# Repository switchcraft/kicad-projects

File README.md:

# kicad-projects
KiCad Project files, schematic files, layout files and netlists

All contributions should adhere to the Kicad library convention, just like the standard KiCad library. 
See: https://github.com/KiCad/kicad-library/wiki/Kicad-Library-Convention

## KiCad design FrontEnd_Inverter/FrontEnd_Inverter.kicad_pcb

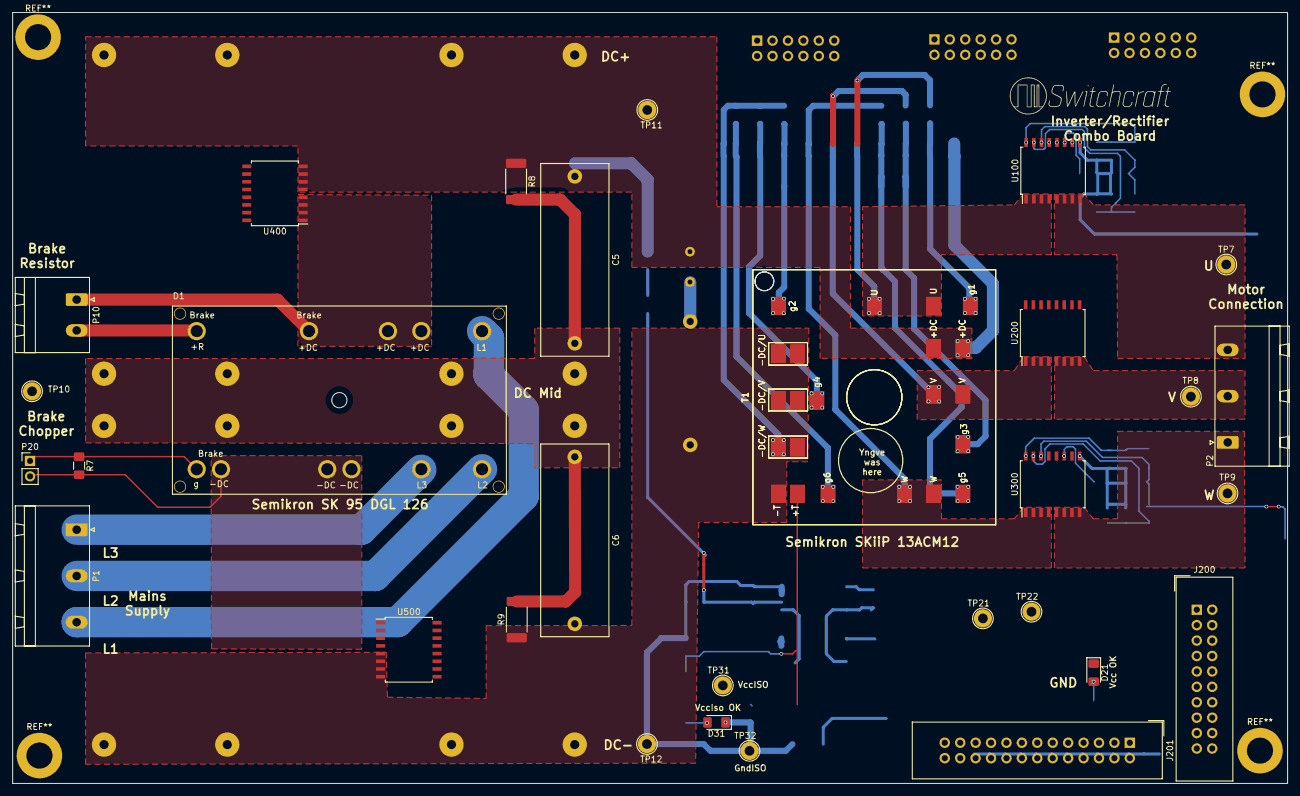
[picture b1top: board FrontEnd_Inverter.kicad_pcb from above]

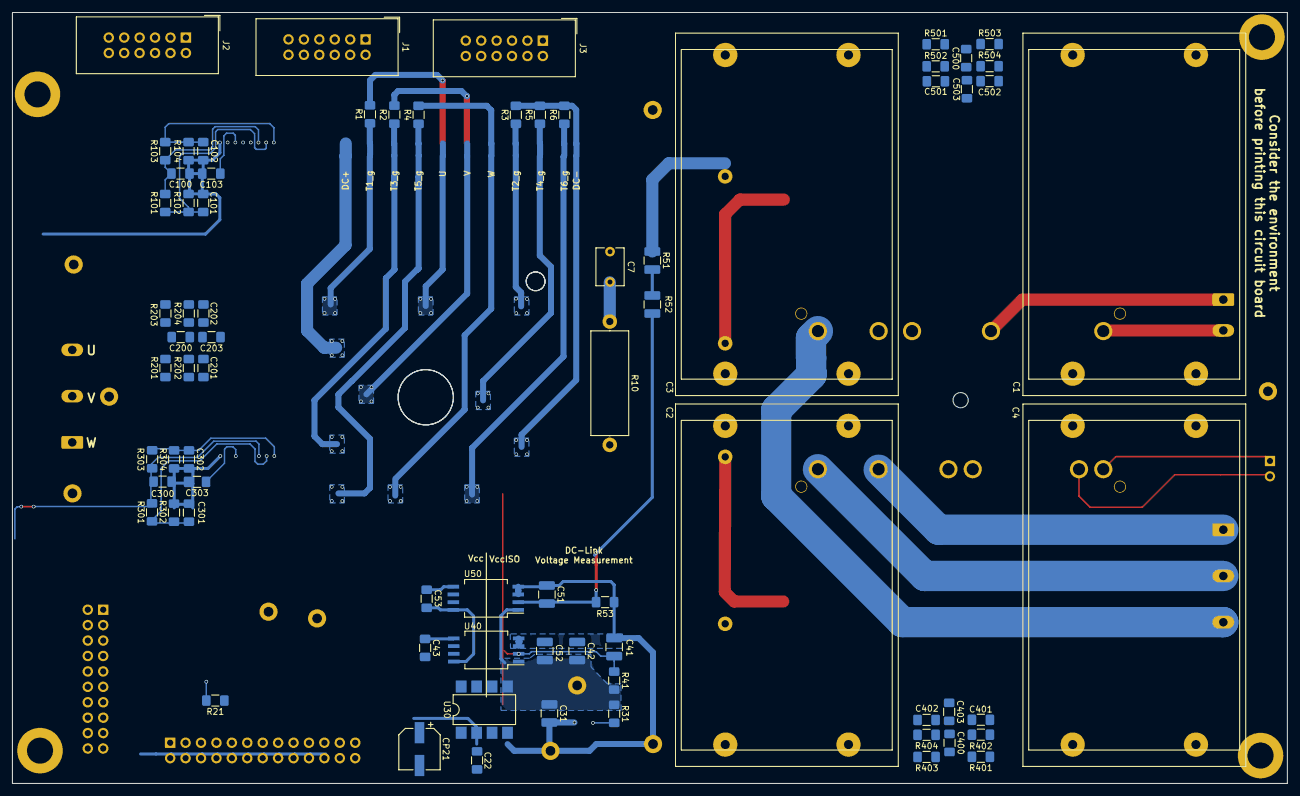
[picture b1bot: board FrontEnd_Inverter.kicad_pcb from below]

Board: 4 copper layers, 210.0 x 127.0 mm, 104 parts (73 on the bottom side), 66 nets.

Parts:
C1, C2, C3, C4: 50uF; Panasonic_EZPE80506MTA
C5, C6: 5uF; C_Rect_L31.5mm_W11.0mm_P27.50mm_MKS4
C7: 22pF; C_Disc_D6.0mm_W4.4mm_P5.00mm
C22: 10nF; C_1206_3216Metric_Pad1.42x1.75mm_HandSolder
C31: 10uF; C_1210_3225Metric_Pad1.42x2.65mm_HandSolder
C41, C51: 100pF; C_1210_3225Metric_Pad1.42x2.65mm_HandSolder
C42, C52: 100nF; C_1210_3225Metric_Pad1.42x2.65mm_HandSolder
C43, C53, C100, C200, C300, C400, C500: 100nF; C_1206_3216Metric_Pad1.42x1.75mm_HandSolder
C101, C102, C103, C201, C202, C203, C301, C302, C303, C401, C402, C403, C501, C502, C503: 1nF; C_1206_3216Metric_Pad1.42x1.75mm_HandSolder
CP21: 10uF; CP_Elec_6.3x7.7
D1: SK_95_DGL_126
D21, D31: GREEN; LED_1206_3216Metric_Pad1.42x1.75mm_HandSolder
J1, J2, J3: GateDriverConn; IDC-Header_2x06_P2.54mm_Vertical
J200: AuxConnector_Analog; IDC-Header_2x10_P2.54mm_Vertical
J201: DigOut_Connector; IDC-Header_2x13_P2.54mm_Vertical
P1, P2: CONN_01X03; PhoenixContact_GMSTBA_2,5_3-G-7,62_1x03_P7.62mm_Horizontal
P10: CONN_01X02; PhoenixContact_MSTBA_2,5_2-G-5,08_1x02_P5.08mm_Horizontal
P20: CONN_01X02; PinHeader_1x02_P2.54mm_Vertical
R1, R2, R3, R4, R5, R6, R7, R41: 100k; R_1206_3216Metric_Pad1.42x1.75mm_HandSolder
R8, R9: 200k; R_2512_6332Metric_Pad1.52x3.35mm_HandSolder
R10: 5; R_Axial_DIN0617_L17.0mm_D6.0mm_P20.32mm_Horizontal
R21, R31: 1250; R_1206_3216Metric_Pad1.42x1.75mm_HandSolder
R51, R52: 2.7M; R_1210_3225Metric_Pad1.42x2.65mm_HandSolder
R53: 20k; R_1206_3216Metric_Pad1.42x1.75mm_HandSolder
R101, R103, R201, R203, R301, R303, R401, R403, R501, R503: 2M; R_1206_3216Metric_Pad1.42x1.75mm_HandSolder
R102, R104, R202, R204, R302, R304, R402, R404, R502, R504: 326k; R_1206_3216Metric_Pad1.42x1.75mm_HandSolder
T1, T1#2: SKiiP_13ACM12V18
TP7: U; TestPoint_Loop_D2.60mm_Drill1.6mm_Beaded
TP8: V; TestPoint_Loop_D2.60mm_Drill1.6mm_Beaded
TP9: W; TestPoint_Loop_D2.60mm_Drill1.6mm_Beaded
TP10: DC_MID; TestPoint_Loop_D2.60mm_Drill1.6mm_Beaded
TP11: DC+; TestPoint_Loop_D2.60mm_Drill1.6mm_Beaded
TP12: DC-; TestPoint_Loop_D2.60mm_Drill1.6mm_Beaded
TP21: VCC; TestPoint_Loop_D2.60mm_Drill1.6mm_Beaded
TP22: GND; TestPoint_Loop_D2.60mm_Drill1.6mm_Beaded
TP31: VCC_ISO; TestPoint_Loop_D2.60mm_Drill1.6mm_Beaded
TP32: GND_ISO; TestPoint_Loop_D2.60mm_Drill1.6mm_Beaded
U30: ISE0505A-H; SMDIP-8_W7.62mm
U40, U50: ACPL-C87B; SSO-8_6.8x5.9mm_P1.27mm_Clearance8mm
U100, U200, U300, U400, U500: ACS720KLATR-35B; SOIC-16W_7.5x10.3mm_P1.27mm

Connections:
+VDC: C1.1, C3.1, C5.1, C7.1, J1.1, J1.2, J2.1, J2.2, J3.1, J3.2, R8.1, R51.1, T1.7, T1.8, T1#2.7, T1#2.8, TP11.1, U400.5, U400.6, U400.7, U400.8
BC_gate: D1.28, P20.1, R7.1
DC+_in: D1.4, D1.5, D1.9, P10.1, U400.1, U400.2, U400.3, U400.4
DC-_in: D1.21, D1.22, D1.27, P20.2, R7.2, U500.1, U500.2, U500.3, U500.4
DC-_out: J1.10, J1.12, J2.10, J2.12, J3.10, J3.12, R2.1, R4.2, R6.2
DC_Meas+: J200.11, U50.7
DC_Meas-: J200.13, U50.6
FAULT_F_DC+: J201.13, U400.13
FAULT_F_DC-: J201.17, U500.13
FAULT_F_U: J201.1, U100.13
FAULT_F_V: J201.5, U200.13
FAULT_F_W: J201.9, U300.13
FAULT_S_DC+: J201.15, U400.10
FAULT_S_DC-: J201.19, U500.10
FAULT_S_U: J201.3, U100.10
FAULT_S_V: J201.7, U200.10
FAULT_S_W: J201.11, U300.10
GND: C22.2, C43.1, C53.2, C100.2, C101.2, C102.2, C103.2, C200.2, C201.2, C202.2, C203.2, C300.2, C301.2, C302.2, C303.2, C400.2, C401.2, C402.2, C403.2, C500.2, C501.2, C502.2, C503.2, CP21.2, D21.1, J200.2, J200.4, J200.6, J200.8, J200.10, J200.12, J200.14, J200.16, J200.18, J200.20, J201.2, J201.4, J201.6, J201.8, J201.10, J201.12, J201.14, J201.16, J201.18, J201.20, J201.22, J201.24, J201.26, R102.1, R104.1, R202.1, R204.1, R302.1, R304.1, R402.1, R404.1, R502.1, R504.1, TP22.1, U30.1, U40.5, U50.5, U100.9, U200.9, U300.9, U400.9, U500.9
unnamed: C1.2, C2.1, C3.2, C4.1, C5.2, C6.1, R8.2, R9.1, TP10.1
unnamed: C7.2, R10.1
unnamed: C51.1, R52.2, R53.1, U50.2
unnamed: C101.1, R101.1, R102.2, U100.15
unnamed: C102.1, R103.1, R104.2, U100.16
unnamed: C103.1, U100.11
unnamed: C201.1, R201.1, R202.2, U200.15
unnamed: C202.1, R203.1, R204.2, U200.16
unnamed: C203.1, U200.11
unnamed: C301.1, R301.1, R302.2, U300.15
unnamed: C302.1, R303.1, R304.2, U300.16
unnamed: C303.1, U300.11
unnamed: C401.1, R401.1, R402.2, U400.15
unnamed: C402.1, R403.1, R404.2, U400.16
unnamed: C403.1, U400.11
unnamed: C501.1, R501.1, R502.2, U500.15
unnamed: C502.1, R503.1, R504.2, U500.16
unnamed: C503.1, U500.11
unnamed: D1.1, P1.3
unnamed: D1.14, P10.2
unnamed: D1.15, P1.2
unnamed: D1.18, P1.1
unnamed: D21.2, R21.2
unnamed: D31.2, R31.2
unnamed: R51.2, R52.1
T1_g: J1.3, J1.4, R1.1, T1.1, T1#2.1
T2_g: J1.9, J1.11, R2.2, T1.2, T1#2.2
T3_g: J2.3, J2.4, R3.1, T1.3, T1#2.3
T4_g: J2.9, J2.11, R4.1, T1.4, T1#2.4
T5_g: J3.3, J3.4, R5.1, T1.5, T1#2.5
T6_g: J3.9, J3.11, R6.1, T1.6, T1#2.6
T+: C41.1, R41.1, T1.21, T1#2.21, U40.2
T+_out: J200.15, U40.7
T-: C2.2, C4.2, C6.2, C31.2, C41.2, C42.1, C51.2, C52.2, D31.1, R9.2, R10.2, R53.2, T1.9, T1.10, T1.11, T1.12, T1.13, T1.14, T1.22, T1#2.9, T1#2.10, T1#2.11, T1#2.12, T1#2.13, T1#2.14, T1#2.22, TP12.1, TP32.1, U30.4, U40.3, U40.4, U50.3, U50.4, U500.5, U500.6, U500.7, U500.8
T-_out: J200.17, U40.6
U: J1.5, J1.6, J1.7, J1.8, R1.2, T1.15, T1.16, T1#2.15, T1#2.16, U100.1, U100.2, U100.3, U100.4
U_out: P2.3, TP7.1, U100.5, U100.6, U100.7, U100.8
V: J2.5, J2.6, J2.7, J2.8, R3.2, T1.17, T1.18, T1#2.17, T1#2.18, U200.1, U200.2, U200.3, U200.4
VCC: C22.1, C43.2, C53.1, C100.1, C200.1, C300.1, C400.1, C500.1, CP21.1, J201.23, R21.1, R101.2, R103.2, R201.2, R203.2, R301.2, R303.2, R401.2, R403.2, R501.2, R503.2, TP21.1, U30.2, U40.8, U50.8, U100.14, U200.14, U300.14, U400.14, U500.14
VCC_ISO: C31.1, C42.2, C52.1, R31.1, R41.2, TP31.1, U30.5, U40.1, U50.1
VI_DC+: J200.7, U400.12
VI_DC-: J200.9, U500.12
VI_U: J200.1, U100.12
VI_V: J200.3, U200.12
VI_W: J200.5, U300.12
V_out: P2.2, TP8.1, U200.5, U200.6, U200.7, U200.8
W: J3.5, J3.6, J3.7, J3.8, R5.2, T1.19, T1.20, T1#2.19, T1#2.20, U300.1, U300.2, U300.3, U300.4
W_out: P2.1, TP9.1, U300.5, U300.6, U300.7, U300.8

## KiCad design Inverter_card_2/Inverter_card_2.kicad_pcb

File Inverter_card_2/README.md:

# Inverter Card 2

Inverter circuit board for Semikron IGBT/SiC module. 

Features connections to gatedrivers and motor output. Voltage and temperature measurement through isolation amplifiers. Three phase output current measurement through hall-effect sensors.

This card is designed to sit on top of the DC-link capacitors. The board is designed for a no-load DC-link voltage of 565V.

## References
DC-link capacitor sizing: <https://www.ecicaps.com/wp-content/uploads/IEMDC_2009_11310_Final_Rev_4.pdf>

## Datasheets

### Capacitors
<http://datasheet.octopart.com/EZP-E80506MTA-Panasonic-datasheet-21212084.pdf>

### Power supply
<http://datasheet.octopart.com/ISE0505A-XP-Power-datasheet-41209557.pdf>

### Sensors
<http://datasheet.octopart.com/ACS758ECB-200U-PFF-T-Allegro-MicroSystems-LLC-datasheet-8491666.pdf>
<http://datasheet.octopart.com/ACPL-C87B-000E-Broadcom-datasheet-68302108.pdf>

### Transistors
<https://www.semikron.com/dl/service-support/downloads/download/semikron-datasheet-skiip-13acm12v18-25238280/>

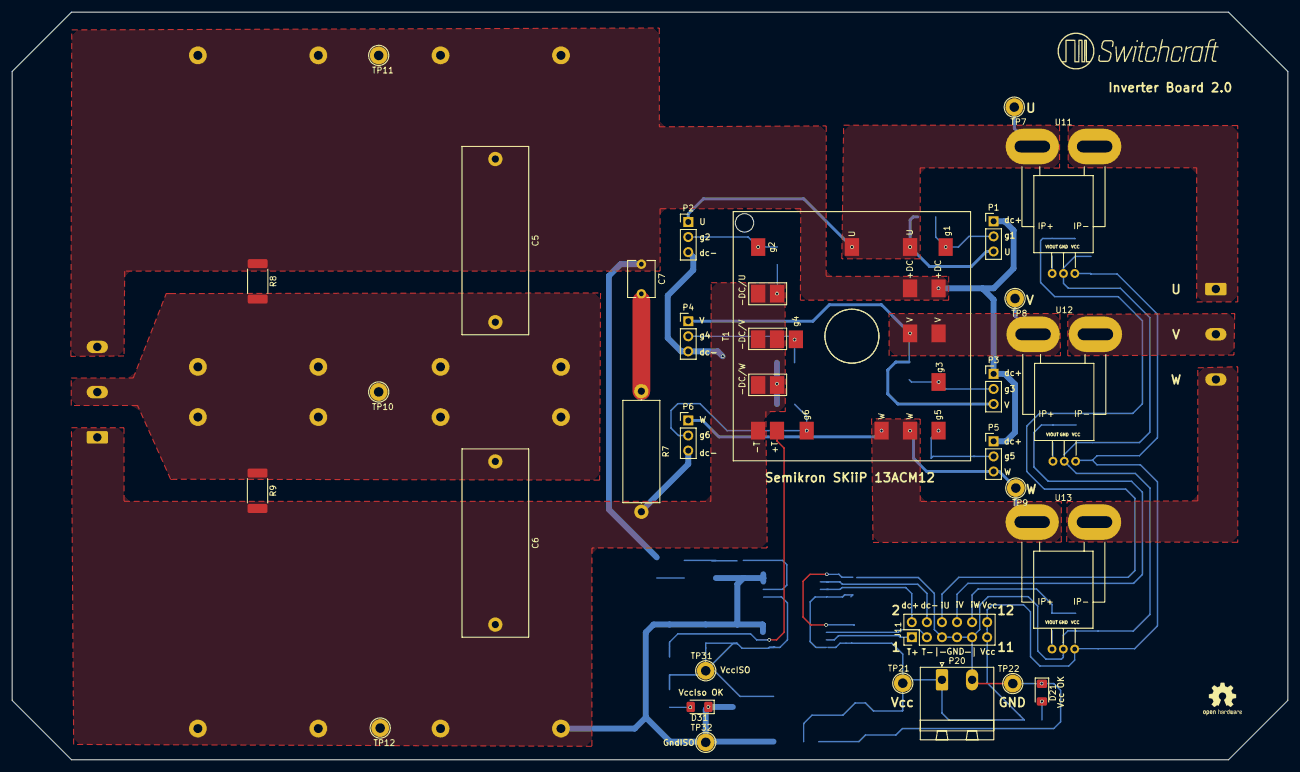
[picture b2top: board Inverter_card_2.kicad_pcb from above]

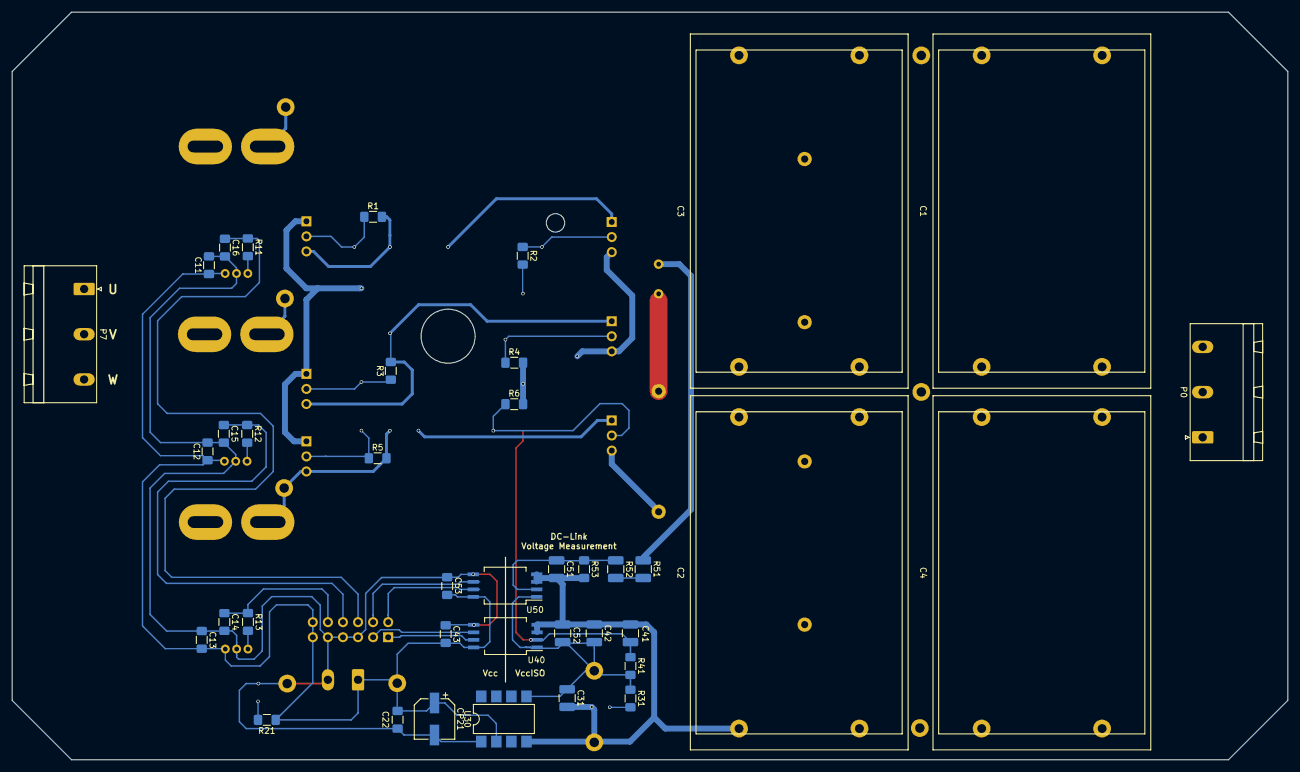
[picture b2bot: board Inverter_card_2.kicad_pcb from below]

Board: 4 copper layers, 215.0 x 126.0 mm, 69 parts (39 on the bottom side), 34 nets.

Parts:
C1, C2, C3, C4: 50uF; Panasonic_EZPE80506MTA
C5, C6: 5uF; C_Rect_L31.5mm_W11.0mm_P27.50mm_MKS4
C7: 22pF; C_Disc_D6.0mm_W4.4mm_P5.00mm
C11, C12, C13, C14, C15, C16, C43, C53: 100nF; C_1206_3216Metric_Pad1.42x1.75mm_HandSolder
C22: 10nF; C_1206_3216Metric_Pad1.42x1.75mm_HandSolder
C31: 10uF; C_1210_3225Metric_Pad1.42x2.65mm_HandSolder
C41, C51: 100pF; C_1210_3225Metric_Pad1.42x2.65mm_HandSolder
C42, C52: 100nF; C_1210_3225Metric_Pad1.42x2.65mm_HandSolder
CP21: 10uF; CP_Elec_6.3x7.7
D21, D31: GREEN; LED_1206_3216Metric_Pad1.42x1.75mm_HandSolder
J11: CONN_02X06; PinHeader_2x06_P2.54mm_Vertical
P0, P7: CONN_01X03; PhoenixContact_GMSTBA_2,5_3-G-7,62_1x03_P7.62mm_Horizontal
P1, P2, P3, P4, P5, P6: CONN_01X03; PinHeader_1x03_P2.54mm_Vertical
P20: CONN_01X02; PhoenixContact_MSTBA_2,5_2-G-5,08_1x02_P5.08mm_Horizontal
R1, R2, R3, R4, R5, R6, R41: 100k; R_1206_3216Metric_Pad1.42x1.75mm_HandSolder
R7: 5; R_Axial_DIN0617_L17.0mm_D6.0mm_P20.32mm_Horizontal
R8, R9: 200k; R_2512_6332Metric_Pad1.52x3.35mm_HandSolder
R11, R12, R13: 250; R_1206_3216Metric_Pad1.42x1.75mm_HandSolder
R21, R31: 1250; R_1206_3216Metric_Pad1.42x1.75mm_HandSolder
R51, R52: 2.7M; R_1210_3225Metric_Pad1.42x2.65mm_HandSolder
R53: 20k; R_1206_3216Metric_Pad1.42x1.75mm_HandSolder
T1: SKiiP_13ACM12V18
TP7, TP8, TP9: TEST; TestPoint_Loop_D2.60mm_Drill1.6mm_Beaded
TP10: DC_MID; TestPoint_Loop_D2.60mm_Drill1.6mm_Beaded
TP11: DC+; TestPoint_Loop_D2.60mm_Drill1.6mm_Beaded
TP12: DC-; TestPoint_Loop_D2.60mm_Drill1.6mm_Beaded
TP21: VCC; TestPoint_Loop_D2.60mm_Drill1.6mm_Beaded
TP22: GND; TestPoint_Loop_D2.60mm_Drill1.6mm_Beaded
TP31: VCC_ISO; TestPoint_Loop_D2.60mm_Drill1.6mm_Beaded
TP32: GND_ISO; TestPoint_Loop_D2.60mm_Drill1.6mm_Beaded
U11, U12, U13: ACS758xCB-PFF; ACS758LCB-050B-PFF-T
U30: ISE0505A-H; SMDIP-8_W7.62mm
U40, U50: ACPL-C87B; SSO-8_6.8x5.9mm_P1.27mm_Clearance8mm

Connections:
DC+: C1.1, C3.1, C5.1, C7.1, P0.3, P1.1, P3.1, P5.1, R8.1, R51.1, T1.7, T1.8, TP11.1
GND: C11.2, C12.2, C13.2, C14.2, C15.2, C16.2, C22.2, C43.1, C53.2, CP21.2, D21.1, J11.5, J11.7, J11.9, P20.2, TP22.1, U11.4, U12.4, U13.4, U30.1, U40.5, U50.5
GND_ISO: C2.2, C4.2, C6.2, C31.2, C41.2, C42.1, C51.2, C52.2, D31.1, P0.1, P2.3, P4.3, P6.3, R2.2, R4.2, R6.2, R7.2, R9.2, R53.2, T1.9, T1.10, T1.11, T1.12, T1.13, T1.14, T1.22, TP12.1, TP32.1, U30.4, U40.3, U40.4, U50.3, U50.4
unnamed: C1.2, C2.1, C3.2, C4.1, C5.2, C6.1, P0.2, R8.2, R9.1, TP10.1
unnamed: C7.2, R7.1
unnamed: C14.1, J11.10, R13.1
unnamed: C15.1, J11.8, R12.1
unnamed: C16.1, J11.6, R11.1
unnamed: C41.1, R41.1, T1.21, U40.2
unnamed: C51.1, R52.2, R53.1, U50.2
unnamed: D21.2, R21.2
unnamed: D31.2, R31.2
unnamed: J11.2, U50.7
unnamed: J11.4, U50.6
unnamed: P7.1, U11.2
unnamed: P7.2, U12.2
unnamed: P7.3, U13.2
unnamed: R11.2, U11.3
unnamed: R12.2, U12.3
unnamed: R13.2, U13.3
unnamed: R51.2, R52.1
T1_g: P1.2, R1.1, T1.1
T2_g: P2.2, R2.1, T1.2
T3_g: P3.2, R3.1, T1.3
T4_g: P4.2, R4.1, T1.4
T5_g: P5.2, R5.1, T1.5
T6_g: P6.2, R6.1, T1.6
T+: J11.1, U40.7
T-: J11.3, U40.6
U: P1.3, P2.1, R1.2, T1.15, T1.16, TP7.1, U11.1
V: P3.3, P4.1, R3.2, T1.17, T1.18, TP8.1, U12.1
VCC: C11.1, C12.1, C13.1, C22.1, C43.2, C53.1, CP21.1, J11.11, J11.12, P20.1, R21.1, TP21.1, U11.5, U12.5, U13.5, U30.2, U40.8, U50.8
VCC_ISO: C31.1, C42.2, C52.1, R31.1, R41.2, TP31.1, U30.5, U40.1, U50.1
W: P5.3, P6.1, R5.2, T1.19, T1.20, TP9.1, U13.1

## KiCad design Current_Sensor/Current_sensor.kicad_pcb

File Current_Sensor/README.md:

# CURRENT SENSOR

This card is the home of the most important current sensors. It otherwise is similar to the VOLT SENSOR project.
Sensor output are rescaled and sent to a sensor input card

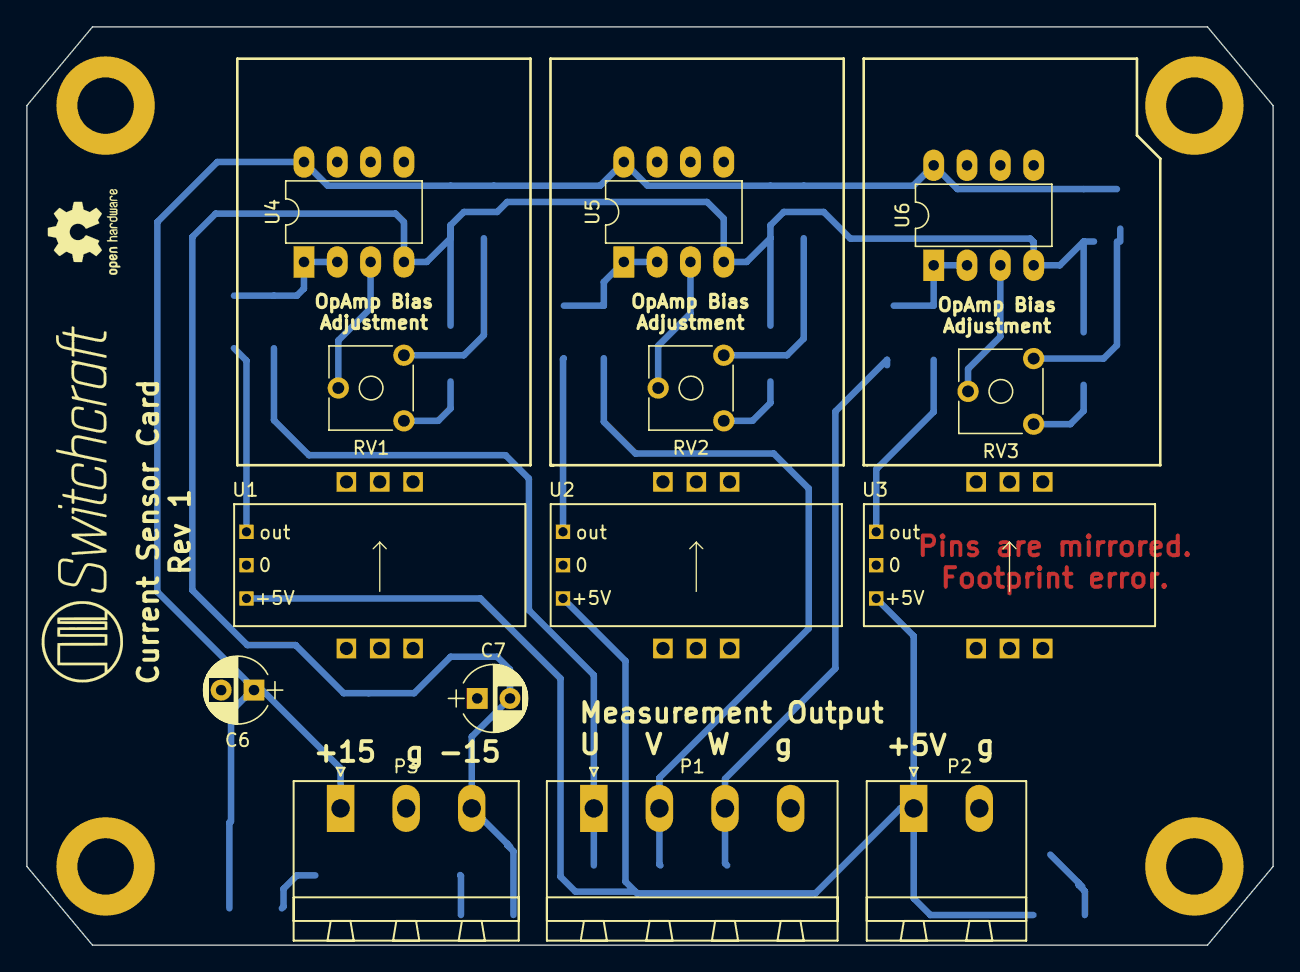
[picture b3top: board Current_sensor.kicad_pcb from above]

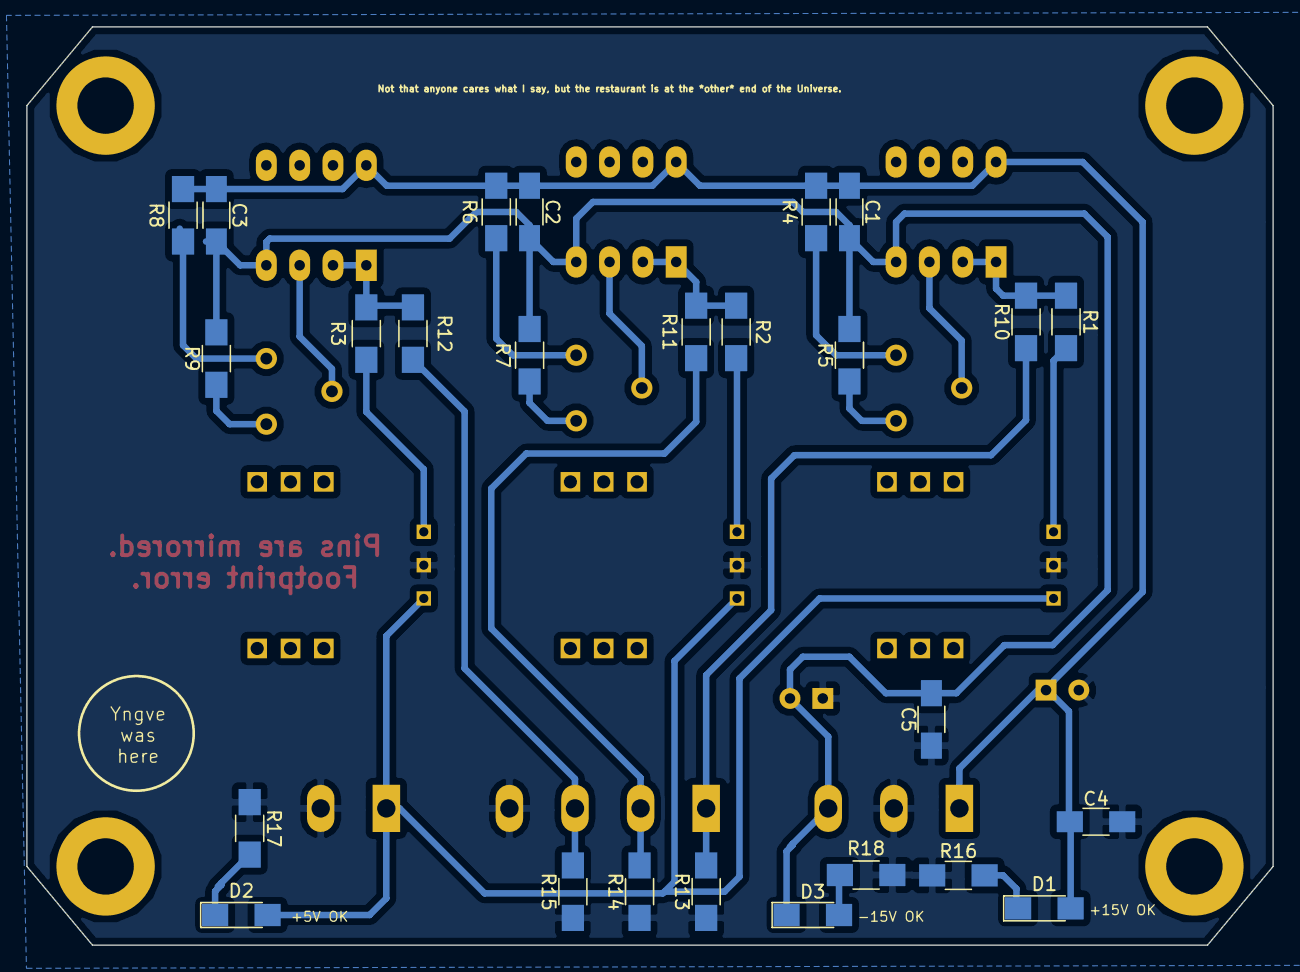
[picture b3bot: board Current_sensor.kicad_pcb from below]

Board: 2 copper layers, 95.0 x 70.0 mm, 40 parts (26 on the bottom side), 25 nets.

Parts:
C1, C2, C3, C4, C5: C; C_1206_HandSoldering
C6, C7: CP; CP_Radial_D5.0mm_P2.50mm
D1, D2, D3: LED; LED_1206_HandSoldering
P1: CONN_01X04; MSTBA_25_4p_G_508-1757268
P2: CONN_01X02; MSTBA_25_2p_G_508-1757242
P3: CONN_01X03; MSTBA_25_3p_G_508-1757488
R1, R2, R3, R4, R5, R6, R7, R8, R9, R10, R11, R12, R13, R14, R15, R16, R17, R18: R; R_1206_HandSoldering
RV1, RV2, RV3: POT; Potentiometer_Trimmer_ACP_CA6v_Horizontal
U1, U2, U3: LTS-25-NP; LTS25-NP
U4, U5, U6: NE5532; DIP-8_W7.62mm_LongPads

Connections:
+5V: D2.2, P2.1, U1.8, U2.8, U3.8
+15V: C1.1, C2.1, C3.1, C4.1, C6.1, D1.2, P3.1, R4.1, R6.1, R8.1, U4.8, U5.8, U6.8
-15V: C1.2, C2.2, C3.2, C5.2, C7.2, D3.1, P3.3, R5.2, R7.2, R9.2, U4.4, U5.4, U6.4
GND: C4.2, C5.1, C6.2, C7.1, P1.4, P2.2, P3.2, R13.1, R14.1, R15.1, R16.1, R17.1, R18.1, U1.9, U2.9, U3.9
unnamed: D1.1, R16.2
unnamed: D2.1, R17.2
unnamed: D3.2, R18.2
unnamed: P1.1, R10.1, R13.2
unnamed: P1.2, R11.1, R14.2
unnamed: P1.3, R12.1, R15.2
unnamed: R1.1, R10.2, U4.1, U4.2
unnamed: R1.2, U1.7
unnamed: R2.2, U2.7
unnamed: R3.2, U3.7
unnamed: R4.2, RV1.1
unnamed: R5.1, RV1.3
unnamed: R6.2, RV2.1
unnamed: R7.1, RV2.3
unnamed: R8.2, RV3.1
unnamed: R9.1, RV3.3
unnamed: R2.1, R11.2, U5.1, U5.2
unnamed: R3.1, R12.2, U6.1, U6.2
unnamed: RV1.2, U4.3
unnamed: RV2.2, U5.3
unnamed: RV3.2, U6.3

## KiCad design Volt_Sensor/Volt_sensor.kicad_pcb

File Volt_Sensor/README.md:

# VOLT SENSOR

This card features voltage sensors and scaling circuits intended to be interfaces with a general measurement input card.

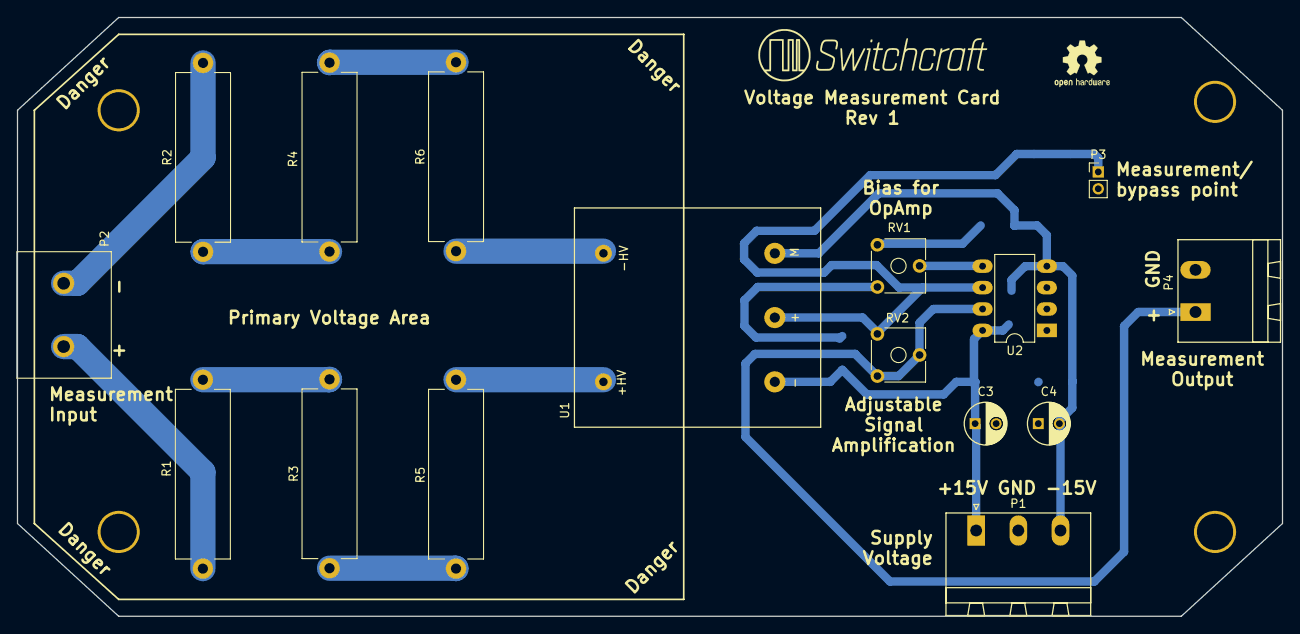
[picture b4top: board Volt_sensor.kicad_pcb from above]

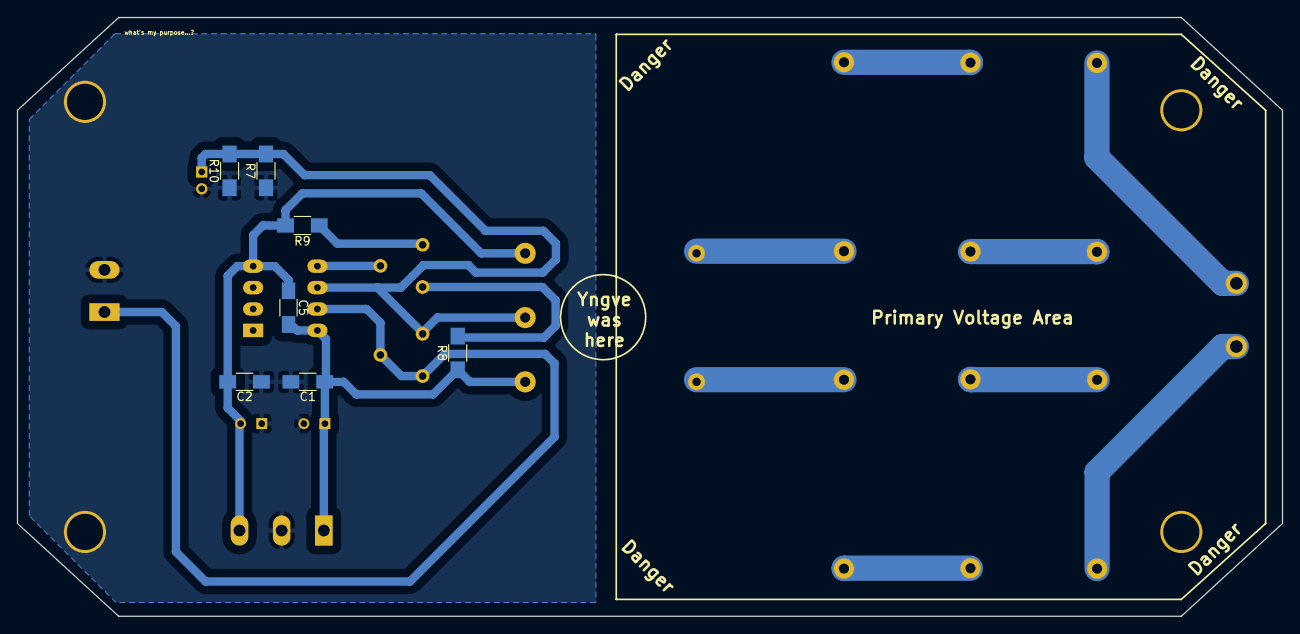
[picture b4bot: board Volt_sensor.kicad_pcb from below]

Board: 2 copper layers, 150.0 x 71.0 mm, 23 parts (7 on the bottom side), 16 nets.

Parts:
C1, C2, C5: 100n; C_1206_HandSoldering
C3, C4: 10u; C_Radial_D5_L11_P2.5
P1: CONN_01X03; MSTBA_25_3p_G_508-1757488
P2: CONN_01X02; GMKDS_3_2p_750-1731022
P3: CONN_01X02; Pin_Header_Straight_1x02_Pitch2.00mm
P4: CONN_01X02; MSTBA_25_2p_G_508-1757242
R1, R2, R3, R4, R5, R6: 10k 5W; R_Axial_Power_L20.0mm_W6.4mm_P22.40mm
R7: 100; R_1206_HandSoldering
R8, R9: 2k; R_1206_HandSoldering
R10: 10k; R_1206_HandSoldering
RV1: 100k; Potentiometer_Trimmer_ACP_CA6v_Horizontal
RV2: 50k; Potentiometer_Trimmer_ACP_CA6v_Horizontal
U1: LV-25-P; LV25-P
U2: NE5532; DIP-8_W7.62mm_LongPads

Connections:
GND: C1.2, C2.1, C3.2, C4.1, P1.2, P3.2, P4.2, R7.1, R10.1
unnamed: P2.1, R2.2
unnamed: P2.2, R1.2
unnamed: P3.1, R7.2, R10.2, RV2.3, U1.4, U2.6
unnamed: P4.1, RV2.1, RV2.2, U2.7
unnamed: R1.1, R3.2
unnamed: R2.1, R4.2
unnamed: R3.1, R5.2
unnamed: R4.1, R6.2
unnamed: R5.1, U1.1
unnamed: R6.1, U1.2
unnamed: R8.2, RV1.1
unnamed: R9.1, RV1.3
unnamed: RV1.2, U2.5
VCC: C1.1, C3.1, C5.2, P1.1, R8.1, U1.3, U2.8
VEE: C2.2, C4.2, C5.1, P1.3, R9.2, U1.5, U2.4

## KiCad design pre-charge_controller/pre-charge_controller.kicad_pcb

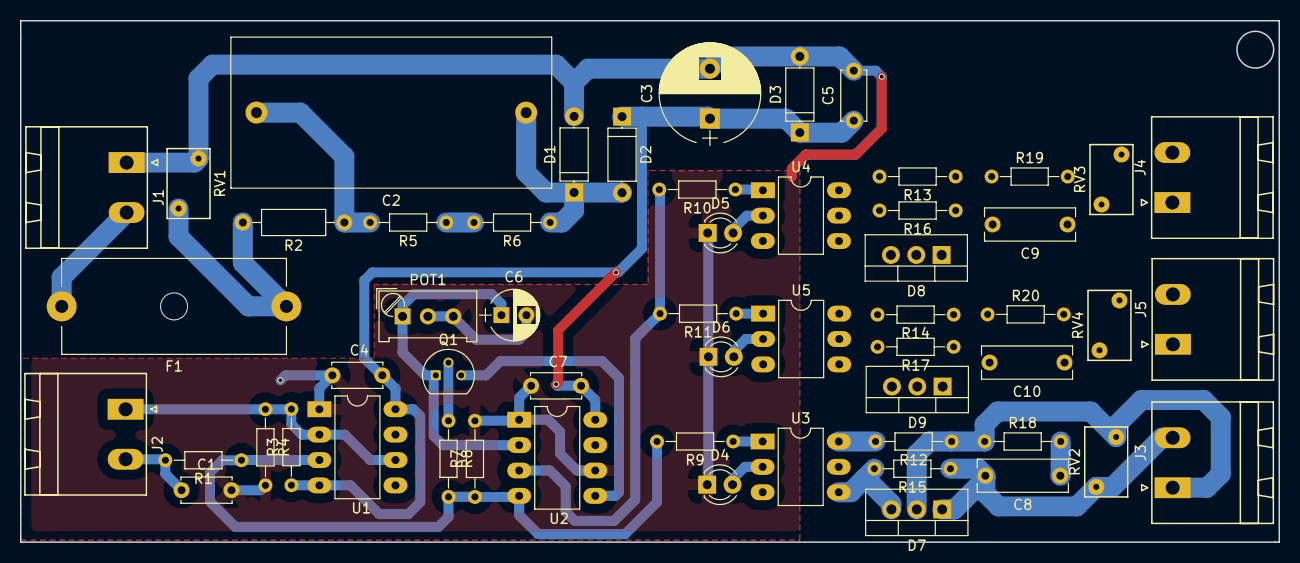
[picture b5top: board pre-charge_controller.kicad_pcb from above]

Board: 2 copper layers, 126.0 x 52.2 mm, 56 parts (0 on the bottom side), 35 nets.

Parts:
C1: 1u; C_Disc_D5.0mm_W2.5mm_P5.00mm
C2: 1uF/400V; C_Rect_L32.0mm_W15.0mm_P27.00mm
C3: 330u; CP_Radial_D10.0mm_P5.00mm
C4, C5, C7: 100n; C_Disc_D5.0mm_W2.5mm_P5.00mm
C6: 10u; CP_Radial_D5.0mm_P2.50mm
C8, C9, C10: 10n; C_Rect_L9.0mm_W3.2mm_P7.50mm_MKT
D1, D2: 1N4007; D_A-405_P7.62mm_Horizontal
D3: D_Zener; D_A-405_P7.62mm_Horizontal
D4, D5, D6: GREEN; LED_D3.0mm
D7, D8, D9: TIC206; TO-220-3_Vertical
F1: Fuse; Fuseholder5x20_horiz_open_Schurter_0031_8201
J1, J2, J3, J4, J5: Conn_01x02; MSTBA_25_2p_G_508-1757242
POT1: 1M; Potentiometer_Trimmer_Bourns_PV36W
Q1: BC556; TO-92_Molded_Narrow
R1: 100k; R_Axial_DIN0204_L3.6mm_D1.6mm_P7.62mm_Horizontal
R2: 100R 1W; R_Axial_DIN0207_L6.3mm_D2.5mm_P10.16mm_Horizontal
R3, R4: 10k; R_Axial_DIN0204_L3.6mm_D1.6mm_P7.62mm_Horizontal
R5, R6: 200k; R_Axial_DIN0204_L3.6mm_D1.6mm_P7.62mm_Horizontal
R7, R9, R10, R11: 1k; R_Axial_DIN0204_L3.6mm_D1.6mm_P7.62mm_Horizontal
R8: 470k; R_Axial_DIN0204_L3.6mm_D1.6mm_P7.62mm_Horizontal
R12, R13, R14, R18, R19, R20: 360R; R_Axial_DIN0204_L3.6mm_D1.6mm_P7.62mm_Horizontal
R15, R16, R17: 330R; R_Axial_DIN0204_L3.6mm_D1.6mm_P7.62mm_Horizontal
RV1, RV2, RV3, RV4: Varistor; RV_Disc_D7_W4.3_P5
U1, U2: LM555; DIP-8_W7.62mm_LongPads
U3, U4, U5: MOC3083M; DIP-6_W7.62mm_LongPads

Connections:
GND: C1.2, C3.2, C4.2, C5.2, C6.2, C7.2, D1.2, D3.2, D4.1, D5.1, D6.1, J1.1, POT1.2, POT1.3, R4.2, R7.2, RV1.2, U1.1, U2.1, U2.6
LINE: F1.1, R2.2, RV1.1
unnamed: C1.1, J2.2, R1.2
unnamed: C2.1, D1.1, D2.2, R6.1
unnamed: C2.2, R2.1, R5.2
unnamed: C6.1, POT1.1, Q1.1, U2.2
unnamed: C8.1, R18.2
unnamed: C8.2, D7.1, J3.2, R15.1, RV2.2
unnamed: C9.1, R19.2
unnamed: C9.2, D8.1, J4.2, R16.1, RV3.2
unnamed: C10.1, R20.2
unnamed: C10.2, D9.1, J5.2, R17.1, RV4.2
unnamed: D4.2, U3.2
unnamed: D5.2, U4.2
unnamed: D6.2, U5.2
unnamed: D7.2, J3.1, R12.1, R18.1, RV2.1
unnamed: D7.3, R15.2, U3.4
unnamed: D8.2, J4.1, R13.1, R19.1, RV3.1
unnamed: D8.3, R16.2, U4.4
unnamed: D9.2, J5.1, R14.1, R20.1, RV4.1
unnamed: D9.3, R17.2, U5.4
unnamed: F1.2, J1.2
unnamed: J2.1, R3.2, R4.1, U1.2, U1.6
unnamed: Q1.2, R8.1
unnamed: Q1.3, U2.5
unnamed: R1.1, R7.1, R8.2, R9.2, U1.3, U2.4
unnamed: R5.1, R6.2
unnamed: R9.1, U3.1
unnamed: R10.1, U4.1
unnamed: R10.2, R11.2, U2.3
unnamed: R11.1, U5.1
unnamed: R12.2, U3.6
unnamed: R13.2, U4.6
unnamed: R14.2, U5.6
VCC: C3.1, C4.1, C5.1, C7.1, D2.1, D3.1, R3.1, U1.4, U1.8, U2.8

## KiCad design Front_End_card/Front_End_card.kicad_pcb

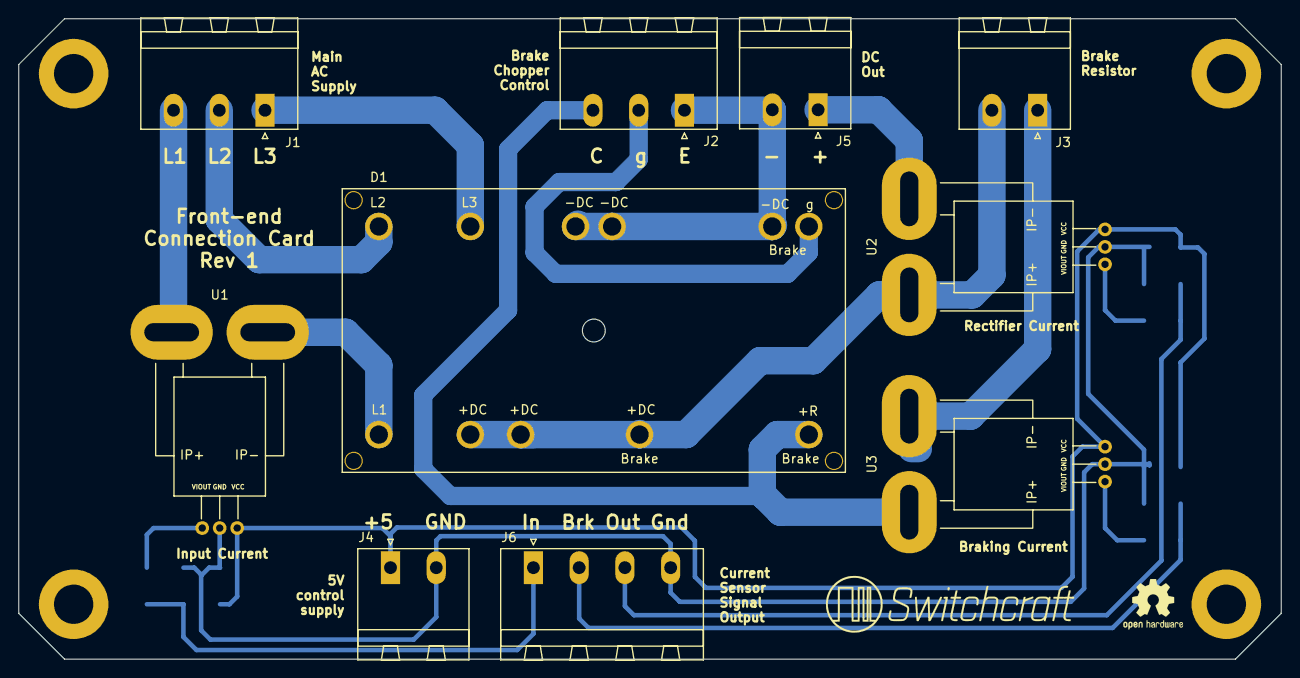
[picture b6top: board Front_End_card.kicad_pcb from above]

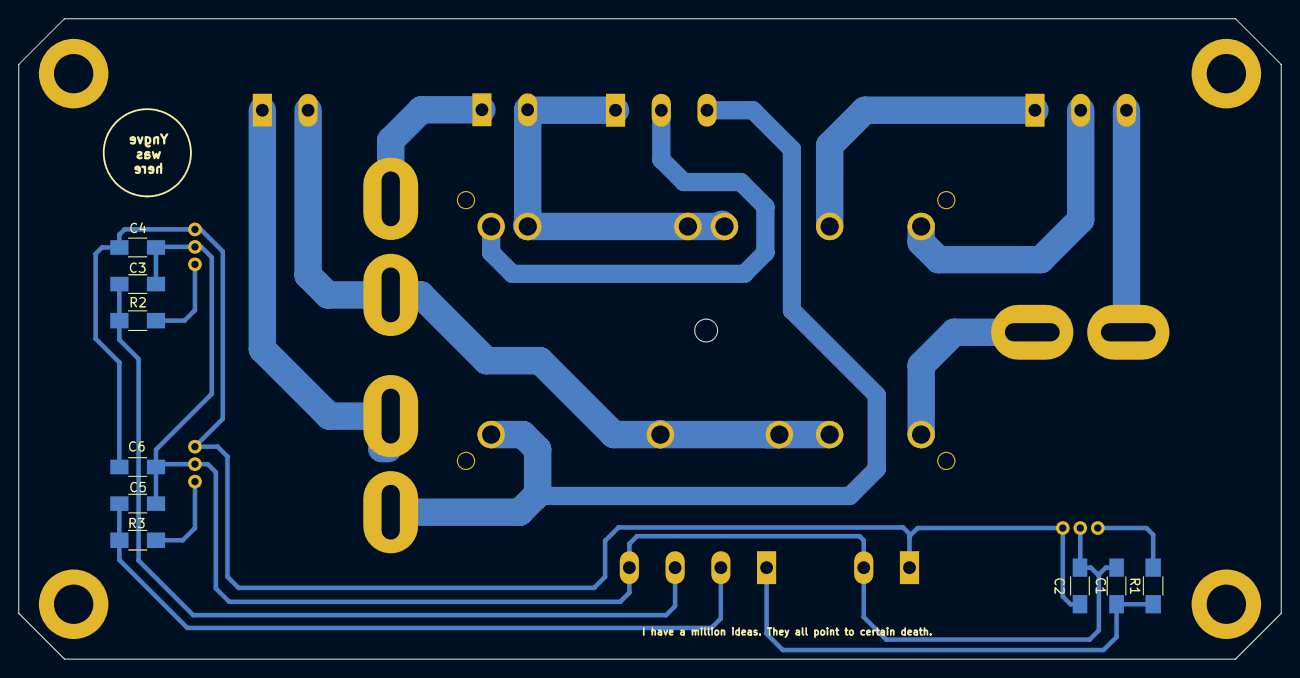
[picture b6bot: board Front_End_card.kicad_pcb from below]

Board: 2 copper layers, 138.0 x 70.0 mm, 19 parts (9 on the bottom side), 18 nets.

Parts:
C1, C3, C5: 0.1uF; C_1206_HandSoldering
C2, C4, C6: C; C_1206_HandSoldering
D1: SK_95_DGL_126
J1, J2: CONN_01X03; MSTBA_25_3p_G_508-1757488
J3, J4, J5: CONN_01X02; MSTBA_25_2p_G_508-1757242
J6: CONN_01X04; MSTBA_25_4p_G_508-1757268
R1, R2, R3: R; R_1206_HandSoldering
U1, U2, U3: ACS758xCB-PFF; ACS758LCB-050B-PFF-T

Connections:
+5V: C2.2, C4.2, C6.2, J4.1, U1.5, U2.5, U3.5
BRAKE: C5.1, J6.2, R3.1
DC_in: C1.1, J6.1, R1.1
DC_out: C3.1, J6.3, R2.1
GND: C1.2, C2.1, C3.2, C4.1, C5.2, C6.1, J4.2, J6.4, U1.4, U2.4, U3.4
unnamed: D1.1, U1.2
unnamed: D1.4, D1.5, D1.9, J3.2, U2.1
unnamed: D1.14, J2.3, U3.1
unnamed: D1.15, J1.2
unnamed: D1.18, J1.1
unnamed: D1.21, D1.22, D1.27, J2.1, J5.2
unnamed: D1.28, J2.2
unnamed: J1.3, U1.1
unnamed: J3.1, U3.2
unnamed: J5.1, U2.2
unnamed: R1.2, U1.3
unnamed: R2.2, U2.3
unnamed: R3.2, U3.3
